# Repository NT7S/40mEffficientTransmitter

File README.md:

# 40mEffficientTransmitter

A crystal-controlled 5 W 40 m CW transmitter built for the 2027 FDIM QRP Transmitter Efficiency Challenge, which scores the DC-to-RF efficiency of the whole transmitter at 12.0 V and 4-6 W into 50 Ω.

The power stage is a single-ended class-E amplifier using an EPC2036 eGaN FET, designed with Sokal's equations and followed by a 3-pole elliptic low-pass filter. A discrete Pierce oscillator on 7.030 MHz, a 5 V Schmitt buffer (SN74LVC1G17) as gate driver, a high-side PMOS keying switch and a TPS62175 buck converter complete the transmitter. In ngspice the PA with its filter delivers 5.10 W at 96.4 % drain efficiency, and the estimated whole-transmitter efficiency is 95.6 %. These are simulation results, not measurements.

The full design justification, simulation results, build plan and test plan are in the [design report](report/report.pdf).

## Status

Prototype, **rev 7**. The PCB layout is complete: 100 × 60 mm, 2-layer, 1.6 mm FR4, designed for JLCPCB (blue soldermask, white silkscreen, ENIG, tented vias). DRC is clean (0 violations, 0 unconnected items, 0 schematic-parity issues). ERC reports 0 errors.

Prototype revisions are numbered (1, 2, 3, ...). Letters, starting from A, are kept for released boards. Revisions 1-6 were first labelled A-F.

| Rev | Was | Change |
|-----|-----|--------|
| 1 | A | Class-E PA stage with tank and L-match, no LPF |
| 2 | B | 3-pole elliptic LPF added |
| 3 | C | Discrete Pierce oscillator replaces the external drive; PMOS keying of the PA rail; trap junctions moved clear of L3 |
| 4 | D | Q3/R4 removed (key shorts R3 to GND); optional R12 shunt with TP1/TP2 and JP1; trimmable oscillator (C9) |
| 5 | E | SMT parts; TPS62175 buck with ferrite-bead filters; footprints and MPNs for every part |
| 6 | F | Probe test points TP4-TP15 with GND pads; DNP gate clamp D1; gate R1/clamp study |
| 7 | - | J1 DC barrel jack (Same Sky PJ-102AH), J4 3.5 mm key jack (Same Sky SJ1-3523N); J2 changed to Molex 0731000105 (DigiKey WM5524-ND) |

Only rev 7 files are in this repository.

## Folders

| Folder | Contents |
|--------|----------|
| [`PCB/`](PCB/) | KiCad 10.0.8 project (`pa40-classe`): schematic, board, custom design rules, project symbol library `pa40.kicad_sym`, project-local footprint libraries in `PCB/lib/` (`pa40.pretty` plus the KiCad stock subset the design uses, including `MountingHole.pretty`), 3-D models in `PCB/pa40.3dshapes/`, layout scripts and notes in `PCB/layout/`, the floorplan in `PCB/floorplan/`, and the JLCPCB Gerber package in [`PCB/production/`](PCB/production/) |
| [`docs/`](docs/) | Schematic PDF and SVG, netlist, ERC and DRC reports, footprint renders, [layout renders](docs/layout/), [datasheet links](docs/datasheets.md) |
| [`bom/`](bom/) | DigiKey BOM with prices and stock (`bom-digikey-rev7.csv`), BOM bulk-add file for one board, and cart file for two boards plus spares |
| [`report/`](report/) | LaTeX source and built PDF of the design report, with the scripts that write its tables |
| [`sim/`](sim/) | ngspice decks and Python scripts for the PA, LPF, keying, oscillator and gate-drive simulations |
| [`print/`](print/) | Printable DigiKey cart checklist, and [JLCPCB order notes](print/jlcpcb-order-notes.md) |
| [`tools/`](tools/) | Schematic and footprint generators, and `export_docs.sh` |

## Building

- Bare boards from JLCPCB. Upload [`PCB/production/pa40-classe-rev7-jlcpcb-gerbers.zip`](PCB/production/pa40-classe-rev7-jlcpcb-gerbers.zip); order parameters and a hole table are in [`PCB/production/README.md`](PCB/production/README.md) (also `print/jlcpcb-order-notes.md`). Parts from DigiKey; the boards are hand-populated.
- Y1 is not in the DigiKey cart. Supply your own 7.030 MHz HC-49 crystal. The footprint takes an HC-49/US crystal, through-hole (4.88 mm lead pitch) or SMD. The BOM part (IQD LFXTAL011525Bulk) is CL 30 pF, but the oscillator simulation assumed CL 20 pF, so trim C9 for frequency.
- L1-L3 are hand-wound toroids (L1 FT-50-61; L2, L3 T80-6) and are not in the DigiKey cart. Winding data is in the report.
- D1 is unfitted. JP1 is a solder jumper: bridge it if R12 is not fitted.
- U2 (TPS62175DQCR) was out of stock at DigiKey on 18 Nov 2026. Check stock and prices in the cart before ordering.

## Regenerating

The committed schematic and footprints already include later in-place edits (L2 pin swap, L1 nylon-screw hole, Etherkit and OSHW logos, courtyard post-processing). Do not re-run `gen.py` or `gen_fp.py` against the live files unless you intend to regenerate from scratch; both assign new UUIDs and `gen_fp.py` would drop the post-processed courtyards.

- Schematic (from scratch only): `gen.py` writes the schematic, the symbol library and `sym-lib-table`. Run it from `PCB/` (`cd PCB && python3 ../tools/gen.py`). It reads KiCad's stock symbols from `/usr/share/kicad/symbols/`.
- Footprints (from scratch only): `python3 tools/gen_fp.py` rewrites `PCB/lib/pa40.pretty`.
- Layout: from `PCB/`, `python3 layout/route.py` reloads the board, strips tracks and zones, and re-routes. Then `sh layout/drc.sh` (needs `kicad-cli`). Top copper photo: `python3 layout/render_cu.py`. 3-D views: `python3 layout/make_3d.py` (pass `--use-board-stackup-colors` is already built in). The latest renders and notes are `PCB/layout/routing-v5-*.png` and `PCB/layout/routing-v5.md`.
- Docs: `tools/export_docs.sh` rewrites the schematic PDF, netlist, SVG, `docs/erc.rpt` and, when the board is present, `docs/drc.rpt` and copies the v5 layout renders into `docs/layout/`.
- Fabrication Gerbers: from the project root, `PCB/production/export.sh` (or `fab/export.sh` in the work tree) writes Gerbers and drill files with JLCPCB's KiCad settings. Zip only the layer files, the two `.drl` files, and the `.gbrjob` as `pa40-classe-rev7-jlcpcb-gerbers.zip`.
- Report: in `report/`, run `python3 gen_tables.py`, `python3 gen_budget_table.py` and `python3 gen_gate_tables.py`, then `latexmk -pdf -jobname=report main.tex`.
- Simulations: the decks in `sim/` run in ngspice. Raw waveform output (`.dat`, `.dat.gz`, `.npz`) is not committed; rerun the scripts to regenerate it.

## License

This work is licensed under the [Creative Commons Attribution-ShareAlike 4.0 International License](https://creativecommons.org/licenses/by-sa/4.0/); see `LICENSE`. Third-party SPICE models in `sim/` keep their original copyright notices and terms.

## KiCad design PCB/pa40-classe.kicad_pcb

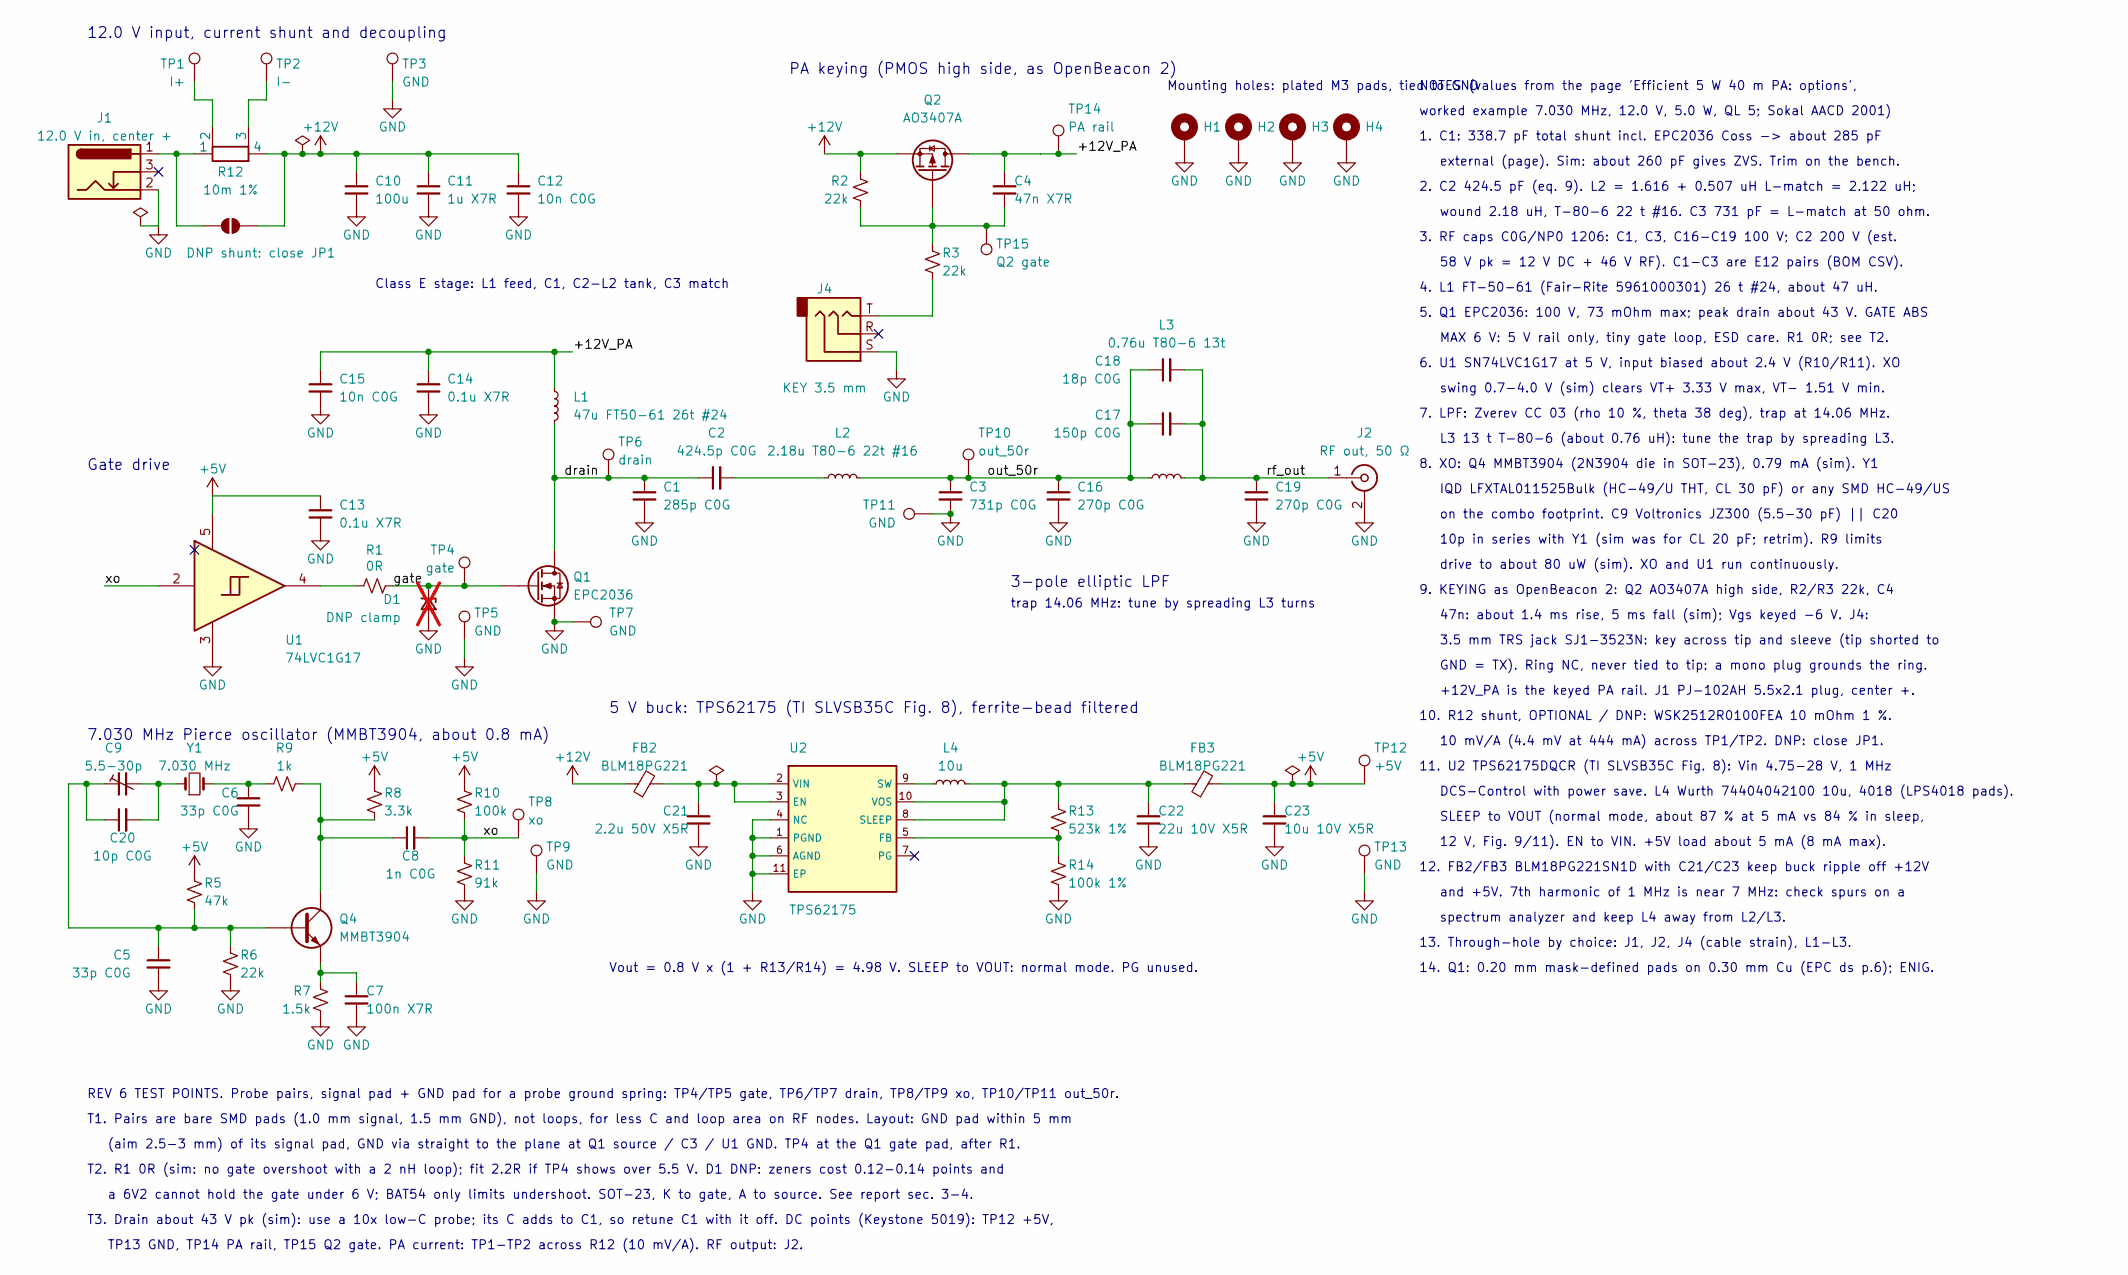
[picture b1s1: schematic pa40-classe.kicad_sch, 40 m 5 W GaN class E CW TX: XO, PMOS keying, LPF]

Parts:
C1: 285p C0G; C_1206_3216Metric; MPN KEMET C1206C271J1GACTU + C1206C150J1GAC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
C2: 424.5p C0G; C_1206_3216Metric; MPN KEMET C1206C391J2GACTU + C1206C330J2GAC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
C3: 731p C0G; C_1206_3216Metric; MPN KEMET C1206C681J1GACTU + C1206C510J1GAC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
C4: 47n X7R; C_0603_1608Metric; MPN Samsung CL10B473KB8NNNC
C5, C6: 33p C0G; C_0603_1608Metric; MPN Murata GRM1885C1H330JA01D
C7: 100n X7R; C_0603_1608Metric; MPN Yageo CC0603KRX7R9BB104
C8: 1n C0G; C_0603_1608Metric; MPN Murata GRM1885C1H102JA01D
C9: 5.5-30p; C_Trimmer_Voltronics_JZ; MPN Knowles Voltronics JZ300
C10: 100u; CP_Elec_6.3x7.7; MPN Panasonic EEE-FK1E101P
C11: 1u X7R; C_0805_2012Metric; MPN Yageo CC0805KKX7R8BB105
C12, C15: 10n C0G; C_0603_1608Metric; MPN Yageo CC0603JRNPO9BN103
C13: 0.1u X7R; C_0603_1608Metric; MPN Yageo CC0603KRX7R9BB104
C14: 0.1u X7R; C_0805_2012Metric; MPN Samsung CL21B104KBCNNNC
C16, C19: 270p C0G; C_1206_3216Metric; MPN KEMET C1206C271J1GACTU
C17: 150p C0G; C_1206_3216Metric; MPN KEMET C1206C151J1GACTU
C18: 18p C0G; C_1206_3216Metric; MPN KEMET C1206C180J1GACTU
C20: 10p C0G; C_0603_1608Metric; MPN Murata GRM1885C1H100JA01D
C21: 2.2u 50V X5R; C_0805_2012Metric; MPN Yageo CC0805KKX5R9BB225
C22: 22u 10V X5R; C_0805_2012Metric; MPN Samsung CL21A226MOQNNNE
C23: 10u 10V X5R; C_0805_2012Metric; MPN Yageo CC0805KRX5R6BB106
D1: DNP clamp; D_SOT-23_A1_K3; MPN DNP: SOT-23 A1/K3 footprint, see note 15; not fitted
FB2, FB3: BLM18PG221; L_0603_1608Metric; MPN Murata BLM18PG221SN1D
H1, H2, H3, H4: MountingHole_Pad; MountingHole_3.2mm_M3_Pad_Via
J1: 12.0 V in, center +; BarrelJack_CUI_PJ-102AH_Horizontal; MPN Same Sky PJ-102AH
J2: RF out, 50 Ω; BNC_Molex_73100-0105_Horizontal; MPN Molex 0731000105
J4: KEY 3.5 mm; Jack_3.5mm_CUI_SJ1-3523N_Horizontal_DS; MPN Same Sky SJ1-3523N
JP1: DNP shunt: close JP1; SolderJumper-2_P1.3mm_Open_RoundedPad1.0x1.5mm
L1: 47u FT50-61 26t #24; L_Toroid_FT50_Flat_P7.62mm_Drill1.0mm; MPN Fair-Rite 5961000301 (FT-50-61)
L2: 2.18u T80-6 22t #16; L_Toroid_T80_Flat_P10.16mm_Drill1.6mm; MPN Micrometals T80-6
L3: 0.76u T80-6 13t; L_Toroid_T80_Flat_P10.16mm_Drill1.6mm; MPN Micrometals T80-6
L4: 10u; L_Coilcraft_LPS4018; MPN Wurth 74404042100
Q1: EPC2036; EPC2036_LGA4_SMD_P0.45mm; MPN EPC EPC2036
Q2: AO3407A; SOT-23; MPN AOS AO3407A
Q4: MMBT3904; SOT-23; MPN onsemi MMBT3904LT1G
R1: 0R; R_0603_1608Metric; MPN Yageo RC0603JR-070RL
R2, R3, R6: 22k; R_0603_1608Metric; MPN Stackpole RMCF0603FT22K0
R5: 47k; R_0603_1608Metric; MPN Yageo RC0603FR-0747KL
R7: 1.5k; R_0603_1608Metric; MPN Yageo RC0603FR-071K5L
R8: 3.3k; R_0603_1608Metric; MPN Yageo RC0603FR-073K3L
R9: 1k; R_0603_1608Metric; MPN Yageo RC0603FR-071KL
R10: 100k; R_0603_1608Metric; MPN Stackpole RMCF0603FT100K
R11: 91k; R_0603_1608Metric; MPN Yageo RC0603FR-0791KL
R12: 10m 1%; R_Shunt_Vishay_WSK2512_6332Metric_T1.19mm; MPN Vishay WSK2512R0100FEA
R13: 523k 1%; R_0603_1608Metric; MPN Yageo RC0603FR-07523KL
R14: 100k 1%; R_0603_1608Metric; MPN Stackpole RMCF0603FT100K
TP1: I+; TestPoint_Keystone_5019_Miniature; MPN Keystone 5019
TP2: I-; TestPoint_Keystone_5019_Miniature; MPN Keystone 5019
TP3, TP13: GND; TestPoint_Keystone_5019_Miniature; MPN Keystone 5019
TP4: gate; TestPoint_Pad_D1.0mm; MPN bare pad, no part
TP5, TP7, TP9, TP11: GND; TestPoint_Pad_D1.5mm; MPN bare pad, no part
TP6: drain; TestPoint_Pad_D1.0mm; MPN bare pad, no part
TP8: xo; TestPoint_Pad_D1.0mm; MPN bare pad, no part
TP10: out_50r; TestPoint_Pad_D1.0mm; MPN bare pad, no part
TP12: +5V; TestPoint_Keystone_5019_Miniature; MPN Keystone 5019
TP14: PA rail; TestPoint_Keystone_5019_Miniature; MPN Keystone 5019
TP15: Q2 gate; TestPoint_Keystone_5019_Miniature; MPN Keystone 5019
U1: 74LVC1G17; SOT-23-5; MPN TI SN74LVC1G17DBVR
U2: TPS62175; WSON-10-1EP_2x3mm_P0.5mm_EP0.84x2.4mm; MPN TI TPS62175DQCR
Y1: 7.030 MHz; Crystal_HC49-US_THT_SMD_Combo; MPN IQD LFXTAL011525Bulk (HC-49/U, CL 30 pF)

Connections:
+5V: C13.1, C23.1, FB3.2, R5.1, R8.1, R10.1, TP12.1, U1.5 (VCC)
+12V: C10.1, C11.1, C12.1, FB2.1, JP1.2 (B), Q2.2 (S), R2.1, R12.4
/+12V_PA: C4.1, C14.1, C15.1, L1.1, Q2.3 (D), TP14.1
/drain: C1.1, C2.1, L1.2, Q1.3 (D), TP6.1
/gate: D1.1 (K), Q1.1 (G), R1.2, TP4.1
/out_50r: C3.1, C16.1, C17.1, C18.1, L2.1, L3.1, TP10.1
/rf_out: C17.2, C18.2, C19.1, J2.1 (In), L3.2
/xo: C8.2, R10.2, R11.1, TP8.1, U1.2
GND: C1.2, C3.2, C5.2, C6.2, C7.2, C10.2, C11.2, C12.2, C13.2, C14.2, C15.2, C16.2, C19.2, C21.2, C22.2, C23.2, D1.2 (A), H1.1, H2.1, H3.1, H4.1, J1.2, J2.2 (Ext), J4.S, Q1.2 (S), Q1.4 (S), R6.2, R7.2, R11.2, R14.2, TP3.1, TP5.1, TP7.1, TP9.1, TP11.1, TP13.1, U1.3 (GND), U2.1 (PGND), U2.4 (NC), U2.6 (AGND), U2.11 (EP)
unnamed: C2.2, L2.2
unnamed: C6.1, R9.1, Y1.2
unnamed: C9.2, C20.2, Y1.1
unnamed: J4.T, R3.2
unnamed: J1.1, JP1.1 (A), R12.1
unnamed: C4.2, Q2.1 (G), R2.2, R3.1, TP15.1
unnamed: C5.1, C9.1, C20.1, Q4.1 (B), R5.2, R6.1
unnamed: C8.1, Q4.3 (C), R8.2, R9.2
unnamed: C7.1, Q4.2 (E), R7.1
unnamed: R1.1, U1.4
unnamed: R12.2, TP1.1
unnamed: R12.3, TP2.1
unnamed: C21.1, FB2.2, U2.2 (VIN), U2.3 (EN)
unnamed: R13.2, R14.1, U2.5 (FB)
unnamed: C22.1, FB3.1, L4.2, R13.1, U2.8 (SLEEP), U2.10 (VOS)
unnamed: L4.1, U2.9 (SW)

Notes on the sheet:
3-pole elliptic LPF
trap 14.06 MHz: tune by spreading L3 turns
PA keying (PMOS high side, as OpenBeacon 2)
7.030 MHz Pierce oscillator (MMBT3904, about 0.8 mA)
5 V buck: TPS62175 (TI SLVSB35C Fig. 8), ferrite-bead filtered
Vout = 0.8 V x (1 + R13/R14) = 4.98 V. SLEEP to VOUT: normal mode. PG unused.
12.0 V input, current shunt and decoupling
Gate drive
Class E stage: L1 feed, C1, C2-L2 tank, C3 match
NOTES (values from the page 'Efficient 5 W 40 m PA: options',
worked example 7.030 MHz, 12.0 V, 5.0 W, QL 5; Sokal AACD 2001)
1. C1: 338.7 pF total shunt incl. EPC2036 Coss -> about 285 pF
external (page). Sim: about 260 pF gives ZVS. Trim on the bench.
2. C2 424.5 pF (eq. 9). L2 = 1.616 + 0.507 uH L-match = 2.122 uH;
wound 2.18 uH, T-80-6 22 t #16. C3 731 pF = L-match at 50 ohm.
3. RF caps C0G/NP0 1206: C1, C3, C16-C19 100 V; C2 200 V (est.
58 V pk = 12 V DC + 46 V RF). C1-C3 are E12 pairs (BOM CSV).
4. L1 FT-50-61 (Fair-Rite 5961000301) 26 t #24, about 47 uH.
5. Q1 EPC2036: 100 V, 73 mOhm max; peak drain about 43 V. GATE ABS
MAX 6 V: 5 V rail only, tiny gate loop, ESD care. R1 0R; see T2.
6. U1 SN74LVC1G17 at 5 V, input biased about 2.4 V (R10/R11). XO
swing 0.7-4.0 V (sim) clears VT+ 3.33 V max, VT- 1.51 V min.
7. LPF: Zverev CC 03 (rho 10 %, theta 38 deg), trap at 14.06 MHz.
L3 13 t T-80-6 (about 0.76 uH): tune the trap by spreading L3.
8. XO: Q4 MMBT3904 (2N3904 die in SOT-23), 0.79 mA (sim). Y1
IQD LFXTAL011525Bulk (HC-49/U THT, CL 30 pF) or any SMD HC-49/US
on the combo footprint. C9 Voltronics JZ300 (5.5-30 pF) || C20
10p in series with Y1 (sim was for CL 20 pF; retrim). R9 limits
drive to about 80 uW (sim). XO and U1 run continuously.
9. KEYING as OpenBeacon 2: Q2 AO3407A high side, R2/R3 22k, C4
47n: about 1.4 ms rise, 5 ms fall (sim); Vgs keyed -6 V. J4:
3.5 mm TRS jack SJ1-3523N: key across tip and sleeve (tip shorted to
GND = TX). Ring NC, never tied to tip: a mono plug grounds the ring.
+12V_PA is the keyed PA rail. J1 PJ-102AH 5.5x2.1 plug, center +.
10. R12 shunt, OPTIONAL / DNP: WSK2512R0100FEA 10 mOhm 1 %.
10 mV/A (4.4 mV at 444 mA) across TP1/TP2. DNP: close JP1.
11. U2 TPS62175DQCR (TI SLVSB35C Fig. 8): Vin 4.75-28 V, 1 MHz
DCS-Control with power save. L4 Wurth 74404042100 10u, 4018 (LPS4018 pads).
SLEEP to VOUT (normal mode, about 87 % at 5 mA vs 84 % in sleep,
12 V, Fig. 9/11). EN to VIN. +5V load about 5 mA (8 mA max).

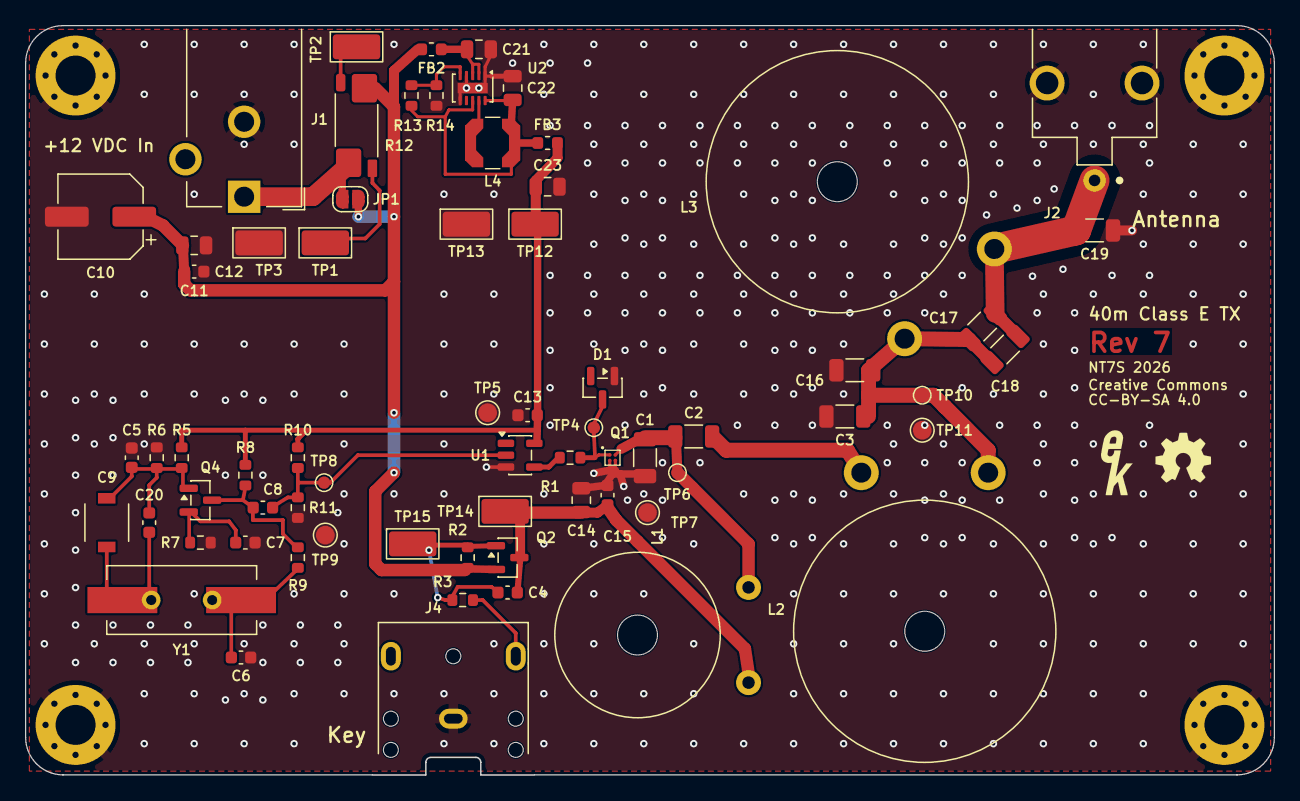
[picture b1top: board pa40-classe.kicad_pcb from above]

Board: 2 copper layers, 100.0 x 60.0 mm, 74 parts (0 on the bottom side), 25 nets.

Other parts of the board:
LOGO1: Val**; EtherkitLogoSmall
LOGO2: Logo_Open_Hardware_Small; OSHWLogo4mm

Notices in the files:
PCB/pa40-classe.kicad_pcb:
CC-BY-SA 4.0
